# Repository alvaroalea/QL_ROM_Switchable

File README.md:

# SINCLAIR QL ROM Adapter with up to 8 Banks.

(C) 2024 Alvaro Alea Fernandez

License under: CERN Open Hardware Licence Version 2 - Strongly Reciprocal

https://ohwr.org/cern_ohl_s_v2.txt

MORE INFO WILL BE ADDED, SOON

WARNING: As is design, is to tall (about 3mm) and do not allow the QL Case to be closed. BE AWARE

## Intro

This board consist in 2 part (shall be 3, really)

A board that replace the 2 ROMS of the Sinclair QL. use a 39SF040 (512kb, 8x64kb, same chip that zx spectrum dandanator)

A board that allow to program the EEPROM Chip in a standar chip programmer.

A optional small board to glue in the outside of Sinclair QL (with dual side tape) and allow easy switch of the ROM, this board is not included, because I use a simple breadboard, with a 4 DIP Switch, and 6 cables that go to 5 back pines of the main board, the 4 pins in the border are not used.

## Instructions

Use female, turn-pin socket in the botton of the board, and 6 male pins on the adapter for the 2x3 conector in the middle, check the height of all.

J2 shall have 3 jumper 1-2, 3-4 and 5-6 for normal use, remove the 3 jumpers to program the chip.

J1 pins 1-2 are to enable the top 16Kb of memory, normally with Toolkit II, remove to use the external ROM Cartridge slot (for QIMSI, MICE and others)
J1 pins 3-4,5-6 and 7-8 allow to select between 8 banks of ROM.
Remove all J1 jumpers to program the chip.

Insert the main board into the programer board, and insert both in the programer to program it.

## The real thing

The board installed on the QL:

Detail of the switch on back to select the ROM:

The adapter on programmer:

The board in the adapter ready to burn, check the J2 without jumpers.

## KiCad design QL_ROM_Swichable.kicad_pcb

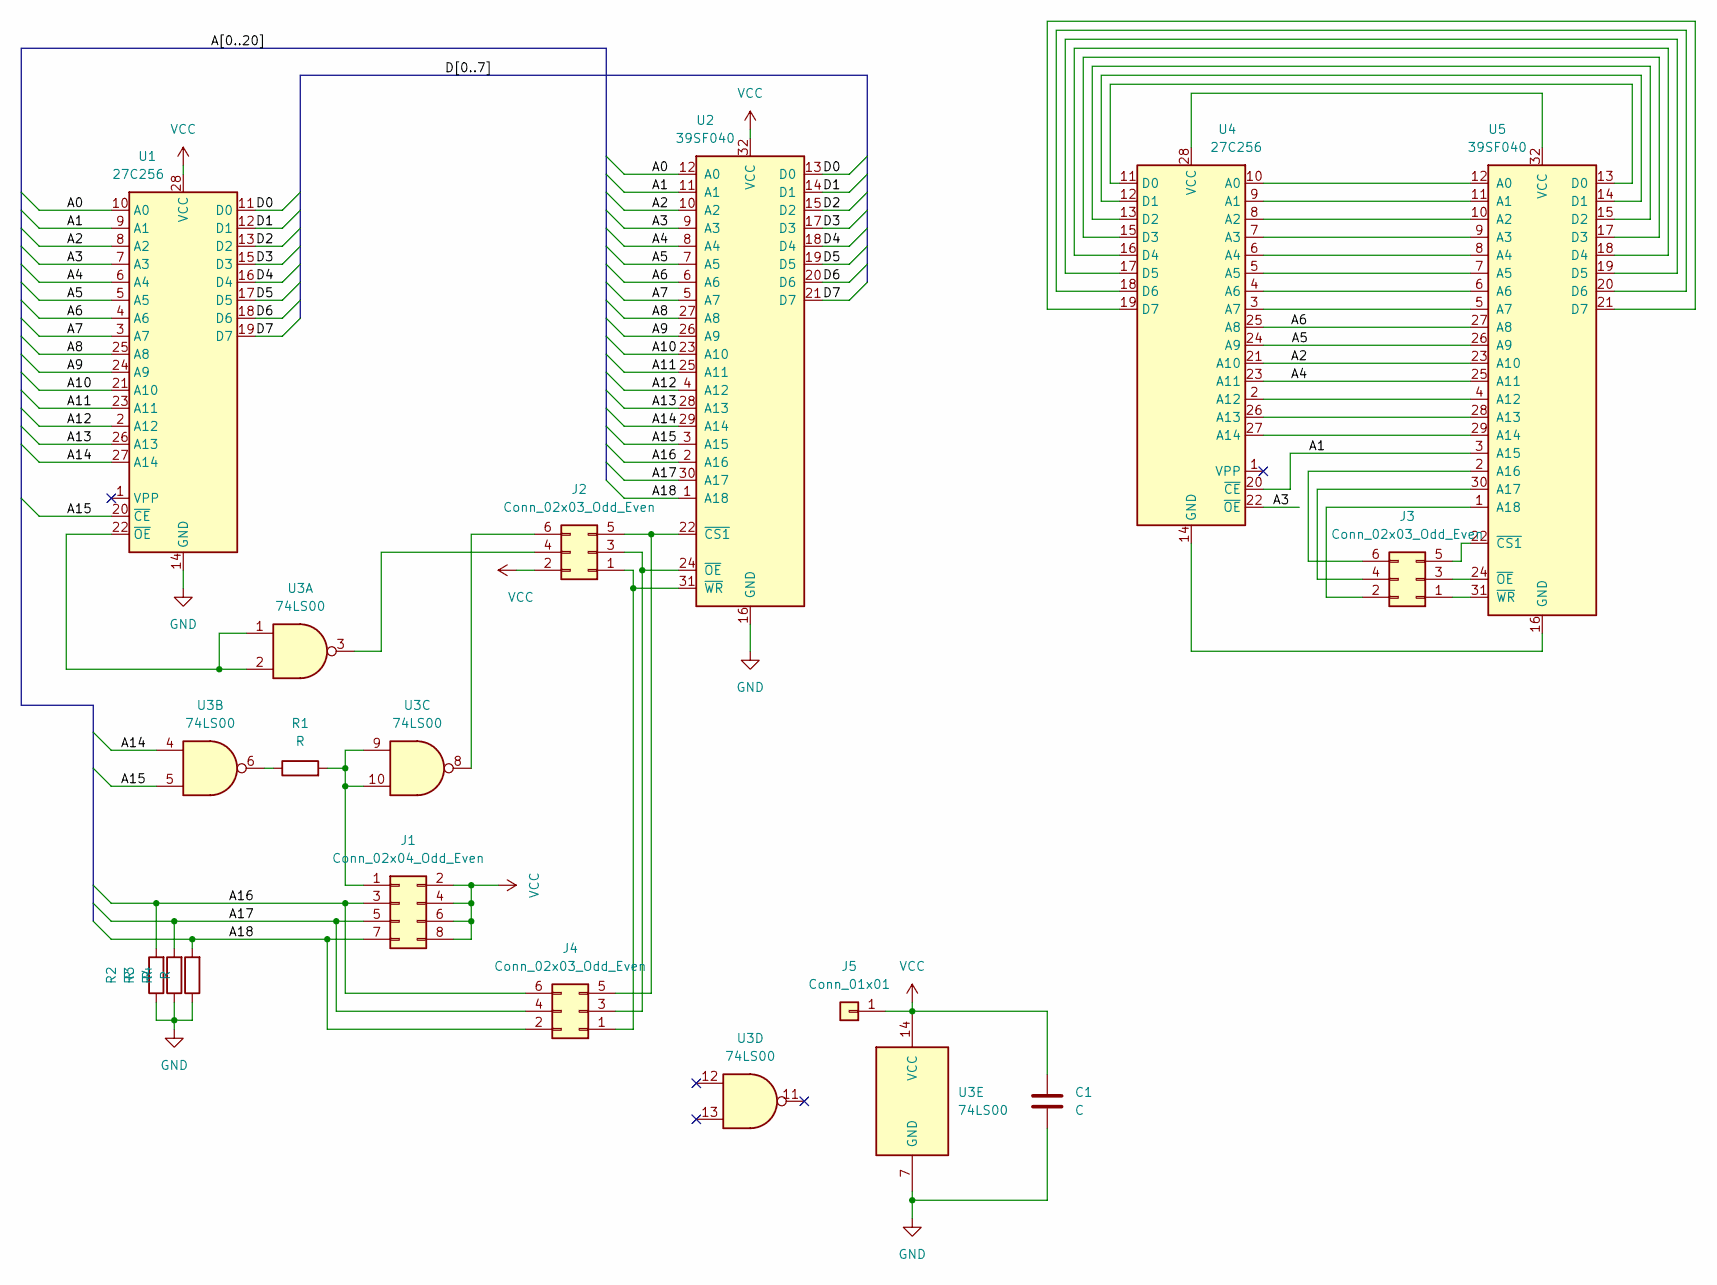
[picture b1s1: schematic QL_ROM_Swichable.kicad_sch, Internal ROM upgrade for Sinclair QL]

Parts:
C1: C; C_Disc_D5.0mm_W2.5mm_P5.00mm
J1: Conn_02x04_Odd_Even; PinHeader_2x04_P2.54mm_Horizontal
J2: Conn_02x03_Odd_Even; PinHeader_1x06_P2.54mm_Horizontal
J3: Conn_02x03_Odd_Even; PinHeader_2x03_P2.54mm_Vertical
J4: Conn_02x03_Odd_Even; PinSocket_2x03_P2.54mm_Vertical
J5: Conn_01x01; PinHeader_1x01_P2.54mm_Vertical
R1, R2, R3, R4: R; R_Axial_DIN0207_L6.3mm_D2.5mm_P7.62mm_Horizontal
U1, U4: 27C256; DIP-28_W15.24mm_Socket
U2: 39SF040; DIP-32_W15.24mm
U3: 74LS00; DIP-14_W7.62mm
U5: 39SF040; DIP-32_W15.24mm_Socket

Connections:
/A0: U1.10 (A0), U2.12 (A0)
/A1: U1.9 (A1), U2.11 (A1), U4.20 (~CE), U5.3 (A15)
/A2: U1.8 (A2), U2.10 (A2), U4.21 (A10), U5.23 (A10)
/A3: U1.7 (A3), U2.9 (A3), U4.22 (~OE)
/A4: U1.6 (A4), U2.8 (A4), U4.23 (A11), U5.25 (A11)
/A5: U1.5 (A5), U2.7 (A5), U4.24 (A9), U5.26 (A9)
/A6: U1.4 (A6), U2.6 (A6), U4.25 (A8), U5.27 (A8)
/A7: U1.3 (A7), U2.5 (A7)
/A8: U1.25 (A8), U2.27 (A8)
/A9: U1.24 (A9), U2.26 (A9)
/A10: U1.21 (A10), U2.23 (A10)
/A11: U1.23 (A11), U2.25 (A11)
/A12: U1.2 (A12), U2.4 (A12)
/A13: U1.26 (A13), U2.28 (A13)
/A14: U1.27 (A14), U2.29 (A14), U3.4
/A15: U1.20 (~CE), U2.3 (A15), U3.5
/A16: J1.3, J4.6, R2.2, U2.2 (A16)
/A17: J1.5, J4.4, R3.2, U2.30 (A17)
/A18: J1.7, J4.2, R4.2, U2.1 (A18)
/D0: U1.11 (D0), U2.13 (D0)
/D1: U1.12 (D1), U2.14 (D1)
/D2: U1.13 (D2), U2.15 (D2)
/D3: U1.15 (D3), U2.17 (D3)
/D4: U1.16 (D4), U2.18 (D4)
/D5: U1.17 (D5), U2.19 (D5)
/D6: U1.18 (D6), U2.20 (D6)
/D7: U1.19 (D7), U2.21 (D7)
GND: C1.2, R2.1, R3.1, R4.1, U1.14 (GND), U2.16 (GND), U3.7 (GND)
unnamed: J1.1, R1.2, U3.9, U3.10
unnamed: J2.1, J4.1, U2.31 (~WR)
unnamed: J2.3, J4.3, U2.24 (~OE)
unnamed: J2.4, U3.3
unnamed: J2.5, J4.5, U2.22 (~CS1)
unnamed: J2.6, U3.8
unnamed: J3.1, U5.31 (~WR)
unnamed: J3.2, U5.1 (A18)
unnamed: J3.3, U5.24 (~OE)
unnamed: J3.4, U5.30 (A17)
unnamed: J3.5, U5.22 (~CS1)
unnamed: J3.6, U5.2 (A16)
unnamed: R1.1, U3.6
unnamed: U1.22 (~OE), U3.1, U3.2
unnamed: U4.10 (A0), U5.12 (A0)
unnamed: U4.9 (A1), U5.11 (A1)
unnamed: U4.8 (A2), U5.10 (A2)
unnamed: U4.7 (A3), U5.9 (A3)
unnamed: U4.6 (A4), U5.8 (A4)
unnamed: U4.5 (A5), U5.7 (A5)
unnamed: U4.4 (A6), U5.6 (A6)
unnamed: U4.3 (A7), U5.5 (A7)
unnamed: U4.2 (A12), U5.4 (A12)
unnamed: U4.26 (A13), U5.28 (A13)
unnamed: U4.27 (A14), U5.29 (A14)
unnamed: U4.11 (D0), U5.13 (D0)
unnamed: U4.12 (D1), U5.14 (D1)
unnamed: U4.13 (D2), U5.15 (D2)
unnamed: U4.15 (D3), U5.17 (D3)
unnamed: U4.16 (D4), U5.18 (D4)
unnamed: U4.17 (D5), U5.19 (D5)
unnamed: U4.18 (D6), U5.20 (D6)
unnamed: U4.19 (D7), U5.21 (D7)
unnamed: U4.14 (GND), U5.16 (GND)
unnamed: U4.28 (VCC), U5.32 (VCC)
VCC: C1.1, J1.2, J1.4, J1.6, J1.8, J2.2, J5.1, U1.28 (VCC), U2.32 (VCC), U3.14 (VCC)

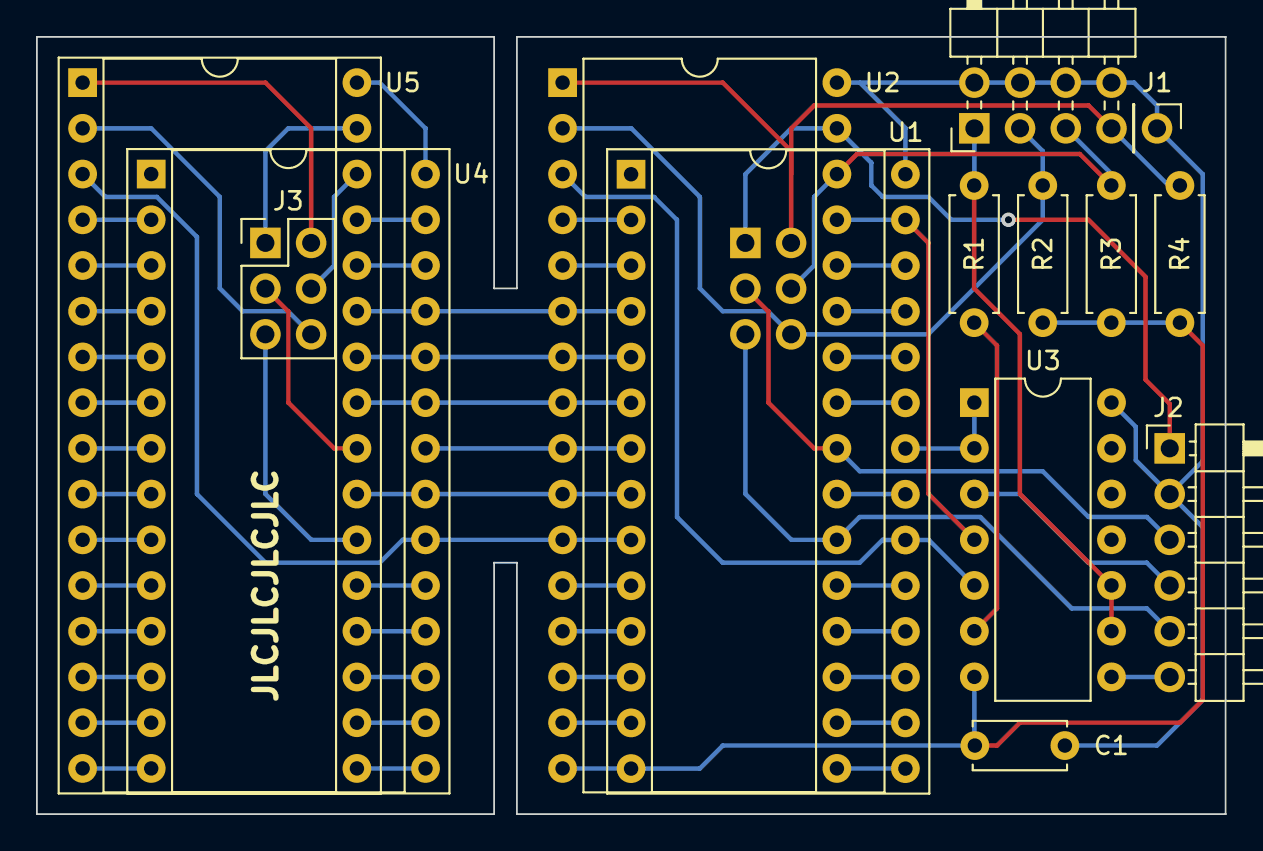
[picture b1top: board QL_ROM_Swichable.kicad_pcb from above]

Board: 2 copper layers, 66.0 x 43.2 mm, 15 parts (1 on the bottom side), 64 nets.

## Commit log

2024-05-12 initial
2024-05-13 photos
2024-05-13 typo
2024-07-09 add pdf

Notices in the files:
QL_ROM_Swichable.kicad_pcb:
(C) 2022 Alvaro Alea
